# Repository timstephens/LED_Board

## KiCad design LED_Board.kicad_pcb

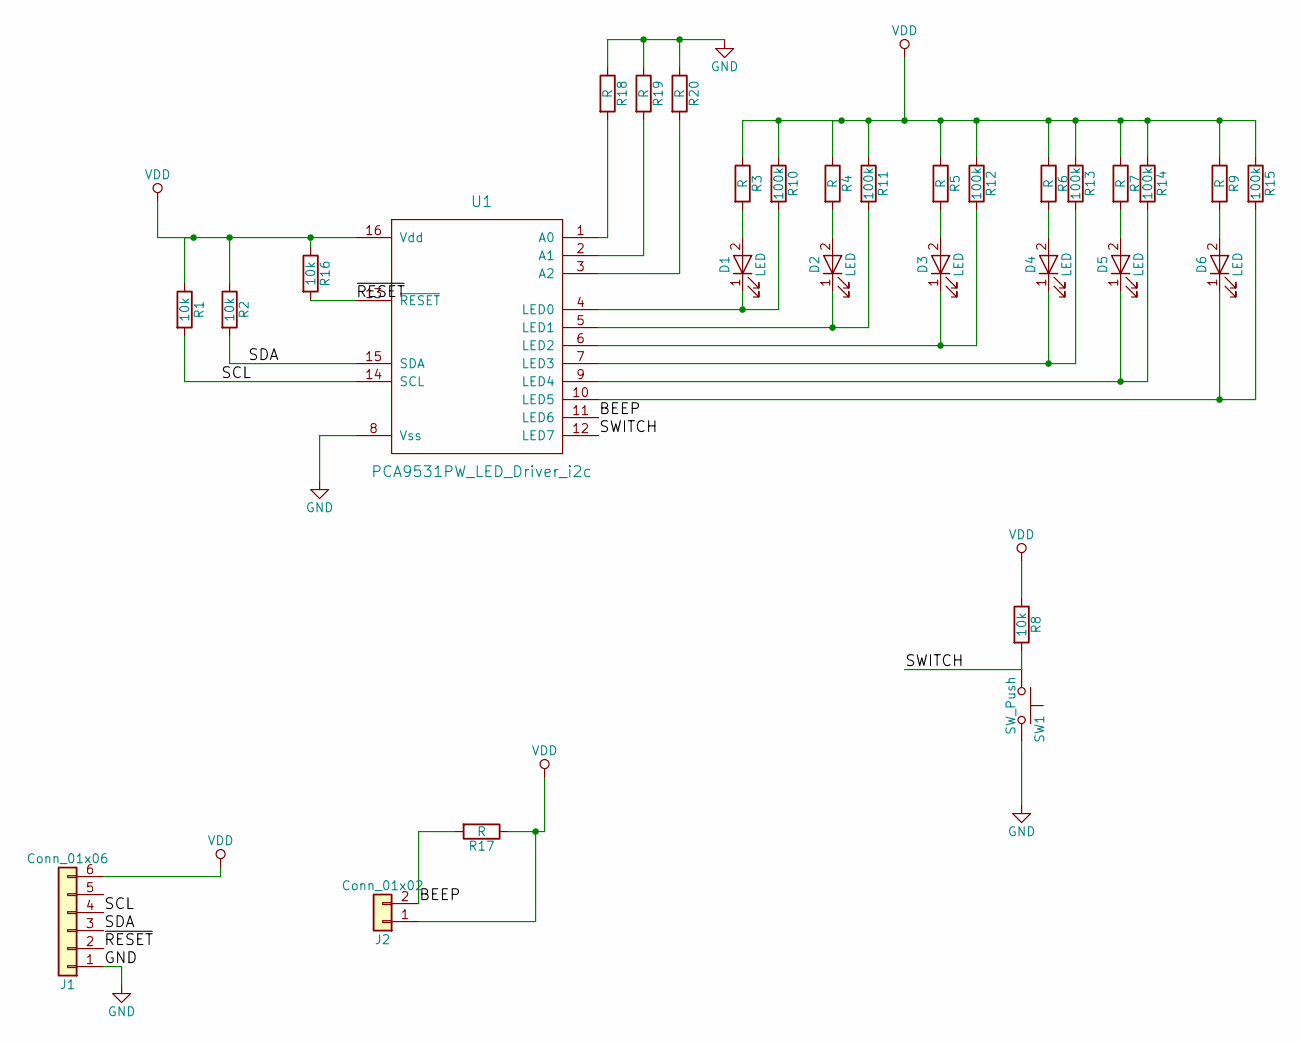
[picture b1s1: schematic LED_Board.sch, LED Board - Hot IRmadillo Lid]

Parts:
D1, D2, D3, D4, D5, D6: LED; LED_1206_HandSoldering
J1: Conn_01x06; Pin_Header_Angled_1x06_Pitch2.54mm
J2: Conn_01x02; Pin_Header_Angled_1x02_Pitch2.54mm
R1, R2, R8, R16: 10k; R_1206_HandSoldering
R3, R4, R5, R6, R7, R9, R17: R; R_1206_HandSoldering
R10, R11, R12, R13, R14, R15: 100k; R_1206_HandSoldering
R18, R19, R20: R; R_1206_Jumper
SW1: SW_Push; SW_PUSH_6mm
U1: PCA9531PW_LED_Driver_i2c; TSSOP-16_4.4x5mm_Pitch0.65mm

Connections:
/BEEP: J2.2, R17.2, U1.11 (LED6)
/SCL: J1.4, R1.2, U1.14 (SCL)
/SDA: J1.3, R2.2, U1.15 (SDA)
/SWITCH: R8.2, SW1.1, U1.12 (LED7)
/~RESET: J1.2, R16.2, U1.13 (~RESET)
GND: J1.1, R18.1, R19.1, R20.1, SW1.2, U1.8 (Vss)
unnamed: D1.1 (K), R10.2, U1.4 (LED0)
unnamed: D1.2 (A), R3.2
unnamed: D2.1 (K), R11.2, U1.5 (LED1)
unnamed: D2.2 (A), R4.2
unnamed: D3.1 (K), R12.2, U1.6 (LED2)
unnamed: D3.2 (A), R5.2
unnamed: D4.1 (K), R13.2, U1.7 (LED3)
unnamed: D4.2 (A), R6.2
unnamed: D5.1 (K), R14.2, U1.9 (LED4)
unnamed: D5.2 (A), R7.2
unnamed: D6.1 (K), R15.2, U1.10 (LED5)
unnamed: D6.2 (A), R9.2
unnamed: R18.2, U1.1 (A0)
unnamed: R19.2, U1.2 (A1)
unnamed: R20.2, U1.3 (A2)
VDD: J1.6, J2.1, R1.1, R2.1, R3.1, R4.1, R5.1, R6.1, R7.1, R8.1, R9.1, R10.1, R11.1, R12.1, R13.1, R14.1, R15.1, R16.1, R17.1, R18.3, R19.3, R20.3, U1.16 (Vdd)

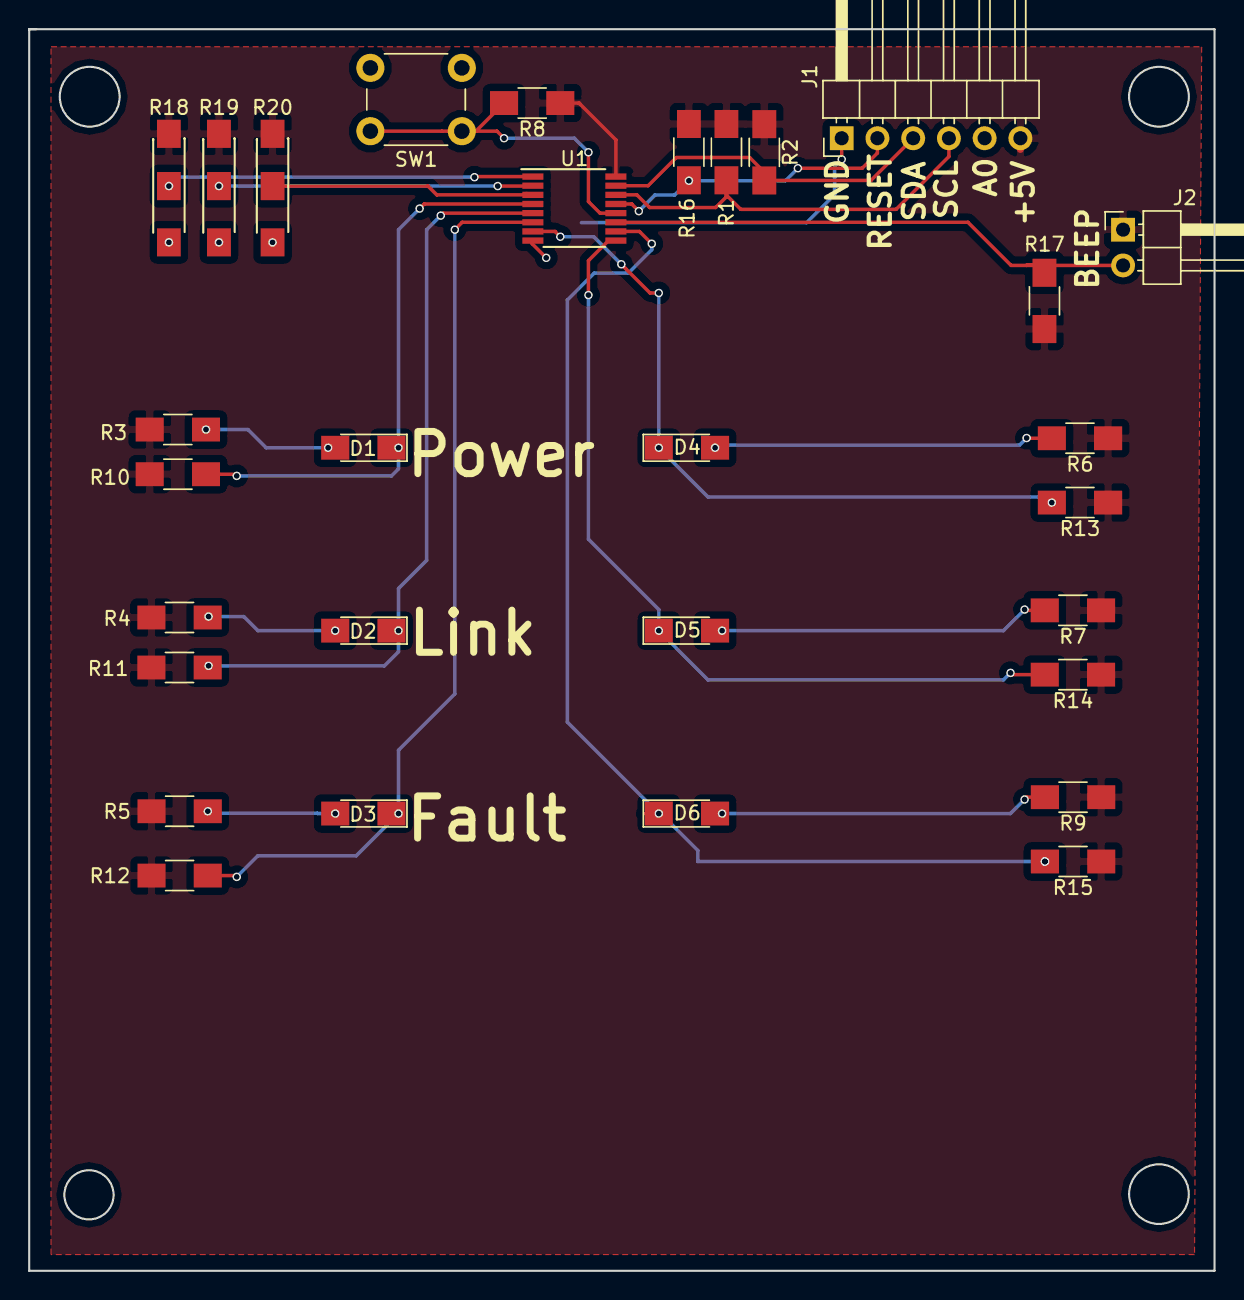
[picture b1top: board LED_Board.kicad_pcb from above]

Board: 2 copper layers, 84.2 x 88.2 mm, 30 parts (0 on the bottom side), 22 nets.

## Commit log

2018-02-21 Added schematic, PCB, etc
    As manufactured (v1)
2018-03-05 Add a cheesy Arduino controller
    A bit of quick Arduino code to read/write the board to see if it's working.
2018-03-08 Arduino code working
    Fixed incorrectly defined pin modes.
    Fixed incorrect startup modes.
    Made sure that it actually sends the commands over i2c
    Added some help text so that I can remember how to control over Serial.
    Tuned the flashing frequencies.
2018-03-09 Arduino code able to read/write
    Fixed a bug that stopped the code reading the status of the input pins.
    Updated the PCB files based on the findings that I made during bring-up.
